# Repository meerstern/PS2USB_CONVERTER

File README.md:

# PS/2 USB逆変換アダプタ
Description of PS/2USB_CONVERTER. 

## 概要
PS/2 USB逆変換アダプタはUSBキーボードをPS/2化する変換アダプタです。  
標準ドライバで動作可能なUSBキーボードをPS/2キーボードとして使用できるように変換します。  
世の中で販売されている変換アダプタとは変換の向きが逆です。  

【市販USBキーボード】<-USB->【PS/2 USB逆変換アダプタ】<-PS/2->【Old PC with PS/2 IF】

プログラミング専用こどもパソコンichigojamやサーバマシンなどのPS/2キーボードのみをサポートしている場合にPS/2 USB逆変換アダプタを使用して、USBキーボードをPS/2化します。

## Ichigojamで使用する場合
IchigoJam Tの場合はそのままキーボード用のUSB端子へPS/2 USB逆変換アダプタを接続してください。  
IchigoJam Uと初代プリント基板の場合は同梱のUSB端子PS/2変換器を介して接続してください。  

## 一般的なコンピュータで使用する場合  
同梱のUSB端子PS/2変換器を介して接続してください。

## 注意
  * USBキーボードをPS/2規格に変換しているため、すべての機器やキー入力を保証することはできません。  
  * すべての機器で対応することを保証できません。  
  * 音量調整やメールボタンといったキーボード固有の機能は使用できません。
  * Logicool製日本語、英語キーボードで動作確認しましたが、すべてのUSBキーボードの動作保証はできません。
  * 日本語、英語以外の言語のキーボードでは入力できないキーがある場合があります。
  * PS/2規格に変換しているため、キーレスポンスやキーリピート等の挙動がUSBで接続する場合と多少異なります。
  * PS/2キーボードとPS/2マウス兼用ポートに接続した場合、不具合が発生する場合はあります。変換ケーブル等でキーボードとマウスを分離して接続してください。
  * USBハブを介した接続には対応していません。直接キーボードのUSBを接続してください。
  * キーレスポンスが遅延する場合は電源投入時リセットに失敗している可能性があります。キーボードのUSBを接続した状態で再度、当該アダプタを抜き差ししてください。  
  * USBマウスとPS/2との変換に非公式で対応しています（コンポジットデバイスでなく、マウスデバイス単体として認識されるマウスのみ対応）    

## 告知
  * 使用ICの価格高騰や入手性を考慮し、STM32+VNC2-32ベース(V1)からPIC32MXベース(V2)に移行しました(22年3月)
  * 使用ICの価格高騰や入手性を考慮し、PIC32MXベース(V2)からWCH CH554ベースに移行予定です(26年秋予定)
  * 移行前の製品と移行後の製品で基本機能は同じですが、キーレスポンス等異なる場合があります  ご了承ください 
  * 上記写真は移行前につき、移行後の製品は若干基板実装部品等異なります  
  * 同梱のPS/2変換器の色や形状、LED色等の仕様を告知なしに変更する場合があります  
  
 ## 販売サイト
  * [スイッチサイエンス][1]
  * [家電のケンちゃん][2]
  * [PCN][3]

## Overview
The PS/2 USB Conversion Adapter is a conversion adapter that converts a USB keyboard to a PS/2 keyboard.  
It converts a USB keyboard that works with standard drivers so that it can be used as a PS/2 keyboard.  
The conversion direction is reversed compared to other conversion adapters sold on the market.  

[Commercial USB Keyboard] <-USB-> [PS/2 USB Conversion Adapter] <-PS/2-> [Old PC with PS/2 IF]

Use the PS/2 USB Conversion Adapter to convert a USB keyboard to PS/2 when the system only supports PS/2 keyboards, such as with the IchigoJam programming computer or server machines.

## Using with IchigoJam
For IchigoJam T, simply connect the PS/2 USB Conversion Adapter to the USB port for the keyboard.  
For IchigoJam U and the original printed circuit board, please connect via the included USB-to-PS/2 converter.  

## When using with a general computer
Please connect via the included USB-to-PS/2 converter.

## Notes
* Because the USB keyboard is converted to the PS/2 standard, we cannot guarantee compatibility with all devices or key inputs.  
* We cannot guarantee compatibility with all devices.  
* Keyboard-specific functions such as volume control and mail buttons cannot be used.  
* We have confirmed operation with Logitech Japanese and English keyboards, but we cannot guarantee operation with all USB keyboards.  
* Some keys may not work with keyboards in languages ​​other than Japanese and English.  
* Because it uses a PS/2 standard conversion, key response and key repeat behavior may differ slightly from when connected via USB.  
* Problems may occur when connecting to a PS/2 keyboard and mouse combined port. Please connect the keyboard and mouse separately using a split cable.  
* Connection via a USB hub is not supported. Please connect the keyboard's USB directly.  
* If key response is delayed, the power-on reset may have failed. Please unplug and replug the adapter while the keyboard's USB is connected.  
* Unofficially supports conversion between USB mice and PS/2 (only mice recognized as standalone mouse devices, not composite devices, are supported).

## Notice
* Due to rising prices and availability of ICs, we have migrated from STM32+VNC2-32 base (V1) to PIC32MX base (V2) (March 2022).  
* Due to rising prices and availability of ICs, we plan to migrate from PIC32MX base (V2) to WCH CH554 base (scheduled for Autumn 2026).  
* While the basic functions are the same for both pre- and post-migration products, key response and other aspects may differ. Please understand.  
* The above photo is from the pre-migration version; the post-migration product will have slightly different components on the circuit board.  
* The color, shape, LED color, and other specifications of the included PS/2 converter may be changed without notice.  
  
[1]: https://www.switch-science.com/products/3785
[2]: https://www.kadenken.com/view/item/000000000767
[3]: https://hello002.stores.jp/items/5bce8ce05f78661b790000ce

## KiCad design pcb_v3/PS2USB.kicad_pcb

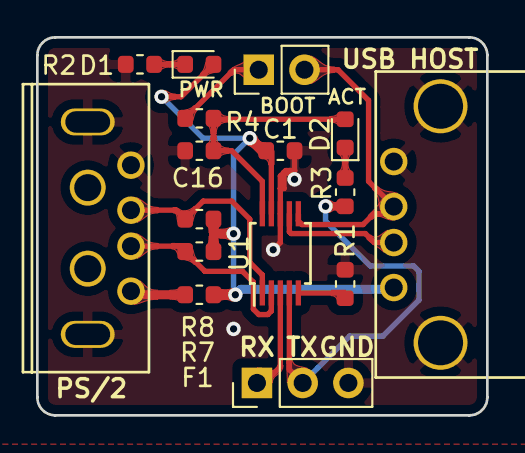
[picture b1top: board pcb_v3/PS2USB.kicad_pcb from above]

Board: 2 copper layers, 25.0 x 21.0 mm, 16 parts (0 on the bottom side), 14 nets.

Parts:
C1, C16: 0.1u; C_0603_1608Metric
D1: PWR; LED_0603_1608Metric
D2: ACT; LED_0603_1608Metric
F1: Fuse; Fuse_0603_1608Metric
JP1: BOOT; PinHeader_1x02_P2.54mm_Vertical
JP2: UART; PinHeader_1x03_P2.54mm_Vertical
P1: USB_PS2; USBA
P2: USB_HOST; USBHOST
R1, R3, R4: 2.2k; R_0603_1608Metric
R2: 3.3k; R_0603_1608Metric
R7, R8: 4.7k; R_0603_1608Metric
U1: CH554E; MSOP-10_3x3mm_P0.5mm

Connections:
+3V3: C16.1, D2.2, R4.2, U1.10
+5V: C1.1, D1.2, F1.2, P2.1, R7.1, R8.1, U1.9
/PSCLK: P1.3, R8.2, U1.1
/PSDAT: P1.2, R7.2, U1.2
/RST: R1.2, U1.5
/RX: JP2.1, U1.3
/TX: JP2.2, R3.2, U1.4
/USB1_DM: P2.2, U1.7
/USB1_DP: JP1.2, P2.3, U1.6
GND: C1.2, C16.2, JP2.3, P1.4, P1.5, P2.4, P2.5, R1.1, R2.2, U1.8
unnamed: D1.1, R2.1
unnamed: D2.1, R3.1
unnamed: F1.1, P1.1
unnamed: JP1.1, R4.1

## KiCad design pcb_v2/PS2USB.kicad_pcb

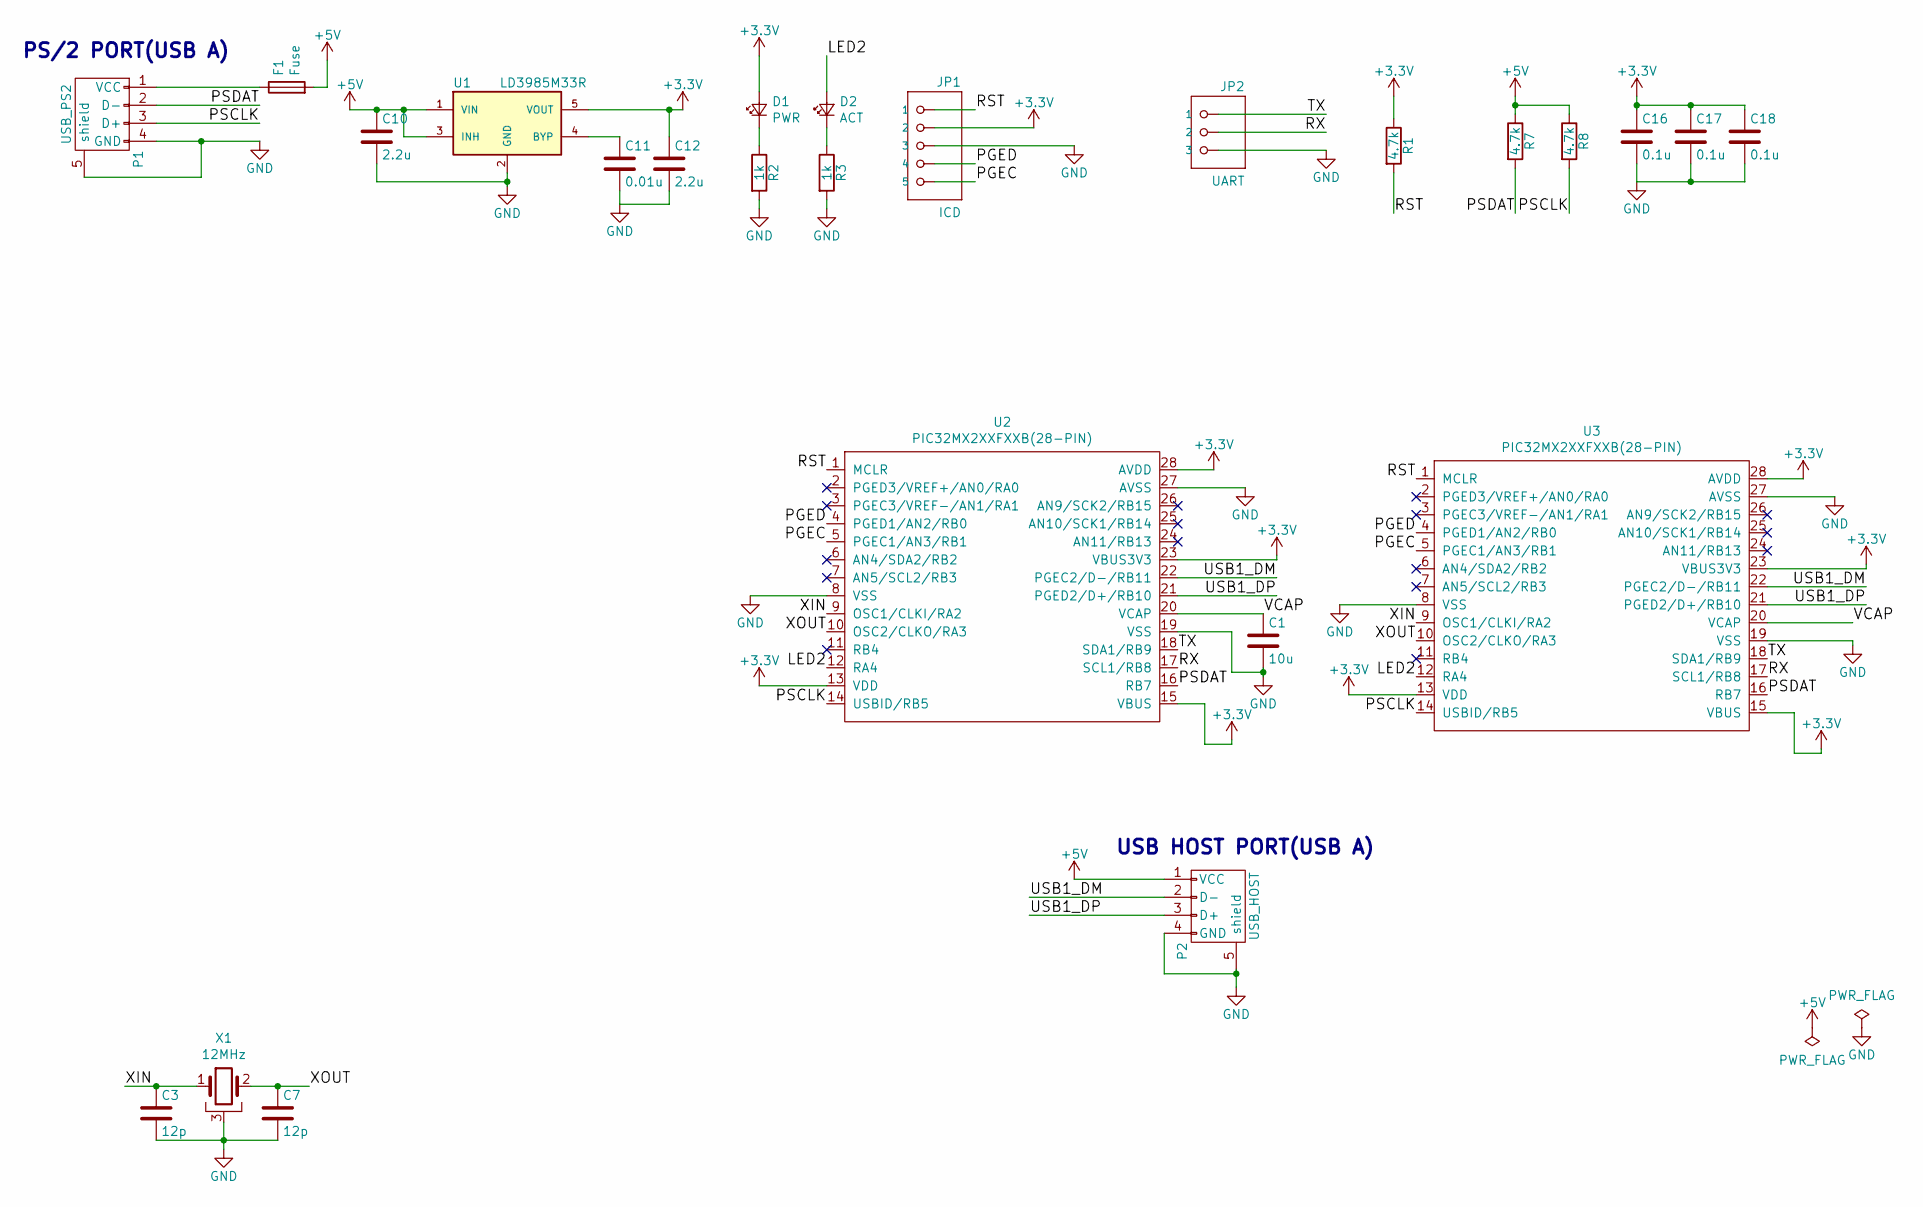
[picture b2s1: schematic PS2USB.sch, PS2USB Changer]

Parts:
C1: 10u; C_0805_2012Metric
C3, C7: 12p; C_0603_1608Metric
C10, C12: 2.2u; C_0603_1608Metric
C11: 0.01u; C_0603_1608Metric
C16, C17, C18: 0.1u; C_0603_1608Metric
D1: PWR; LED_0603_1608Metric
D2: ACT; LED_0603_1608Metric
F1: Fuse; Fuse_0603_1608Metric
JP1: ICD; PinHeader_1x05_P2.54mm_Vertical
JP2: UART; PinHeader_1x03_P2.54mm_Vertical
P1: USB_PS2; USBA
P2: USB_HOST; USBHOST
R1, R7, R8: 4.7k; R_0603_1608Metric
R2, R3: 1k; R_0603_1608Metric
U1: LD3985M33R; SOT-23-5
U2: PIC32MX2XXFXXB(28-PIN); SSOP-28_5.3x10.2mm_P0.65mm
U3: PIC32MX2XXFXXB(28-PIN); SOIC-28W_7.5x17.9mm_P1.27mm
X1: 12MHz; FA238V

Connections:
+3V3: C12.1, C16.1, C17.1, C18.1, D1.2 (A), JP1.2, R1.1, U1.5 (VOUT), U2.13 (VDD), U2.15 (VBUS), U2.23 (VBUS3V3), U2.28 (AVDD), U3.13 (VDD), U3.15 (VBUS), U3.23 (VBUS3V3), U3.28 (AVDD)
+5V: C10.1, F1.2, P2.1 (VCC), R7.1, R8.1, U1.1 (VIN), U1.3 (INH)
/LED2: D2.2 (A), U2.12 (RA4), U3.12 (RA4)
/PGEC: JP1.5, U2.5 (PGEC1/AN3/RB1), U3.5 (PGEC1/AN3/RB1)
/PGED: JP1.4, U2.4 (PGED1/AN2/RB0), U3.4 (PGED1/AN2/RB0)
/PSCLK: P1.3 (D+), R8.2, U2.14 (USBID/RB5), U3.14 (USBID/RB5)
/PSDAT: P1.2 (D-), R7.2, U2.16 (RB7), U3.16 (RB7)
/RST: JP1.1, R1.2, U2.1 (MCLR), U3.1 (MCLR)
/RX: JP2.2, U2.17 (SCL1/RB8), U3.17 (SCL1/RB8)
/TX: JP2.1, U2.18 (SDA1/RB9), U3.18 (SDA1/RB9)
/USB1_DM: P2.2 (D-), U2.22 (PGEC2/D-/RB11), U3.22 (PGEC2/D-/RB11)
/USB1_DP: P2.3 (D+), U2.21 (PGED2/D+/RB10), U3.21 (PGED2/D+/RB10)
/VCAP: C1.1, U2.20 (VCAP), U3.20 (VCAP)
/XIN: C3.1, U2.9 (OSC1/CLKI/RA2), U3.9 (OSC1/CLKI/RA2), X1.1
/XOUT: C7.1, U2.10 (OSC2/CLKO/RA3), U3.10 (OSC2/CLKO/RA3), X1.2
GND: C1.2, C3.2, C7.2, C10.2, C11.2, C12.2, C16.2, C17.2, C18.2, JP1.3, JP2.3, P1.4 (GND), P1.5 (shield), P2.4 (GND), P2.5 (shield), R2.2, R3.2, U1.2 (GND), U2.8 (VSS), U2.19 (VSS), U2.27 (AVSS), U3.8 (VSS), U3.19 (VSS), U3.27 (AVSS), X1.3
unnamed: C11.1, U1.4 (BYP)
unnamed: D1.1 (K), R2.1
unnamed: D2.1 (K), R3.1
unnamed: F1.1, P1.1 (VCC)

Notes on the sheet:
PS/2 PORT(USB A)
USB HOST PORT(USB A)

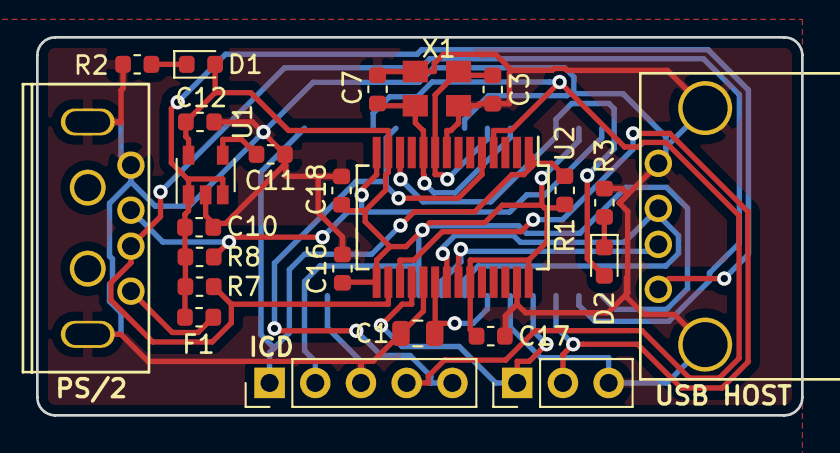
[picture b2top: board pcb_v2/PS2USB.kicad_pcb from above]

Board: 2 copper layers, 42.5 x 21.0 mm, 25 parts (1 on the bottom side), 20 nets.

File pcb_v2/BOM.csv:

Elecrow PN,Parts,Value,Package,QTY,Digikey/Mouser/Manufacturer Part,Remark/ Link
4040806A,"D1,D2",LED,LED_0603_1608Metric,2,,
,U1,LD3985M33R,SOT-23-5,1,511-LD3985M33R,
C23162,"R1,R7,R8",4.7k,R_0603_1608Metric,3,,
C15850,C1,10u,C_0805_2012Metric,1,,
,P1,USB_PS2,USBA,1,490-UP2-AH-1-TH,
,F1,Fuse,Fuse_0603_1608Metric,1,650-FEMTOSMDC035F-02,
C14663,"C18,C17,C16",0.1u,C_0603_1608Metric,3,,
2014022A,"C12,C10",2.2u,C_0603_1608Metric,2,,
C57112,C11,0.01u,C_0603_1608Metric,1,,
C1644,"C7,C3",10p,C_0603_1608Metric,2,,
,P2,USB_HOST,USBHOST,1,530-SS-52100-001,
C21190,"R2,R3",1k,R_0603_1608Metric,2,,
,X1,12MHz,FA238V,1,ECS-120-12-33-AGN-TR3,
,U2,PIC32MX2XXFXXB(28-PIN),SSOP-28_5.3x10.2mm_P0.65mm,1,579-MX230F256B50I/SS,

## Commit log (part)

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2018-03-18 Init
2022-03-24 Add files
2026-06-04 Add v3 files
